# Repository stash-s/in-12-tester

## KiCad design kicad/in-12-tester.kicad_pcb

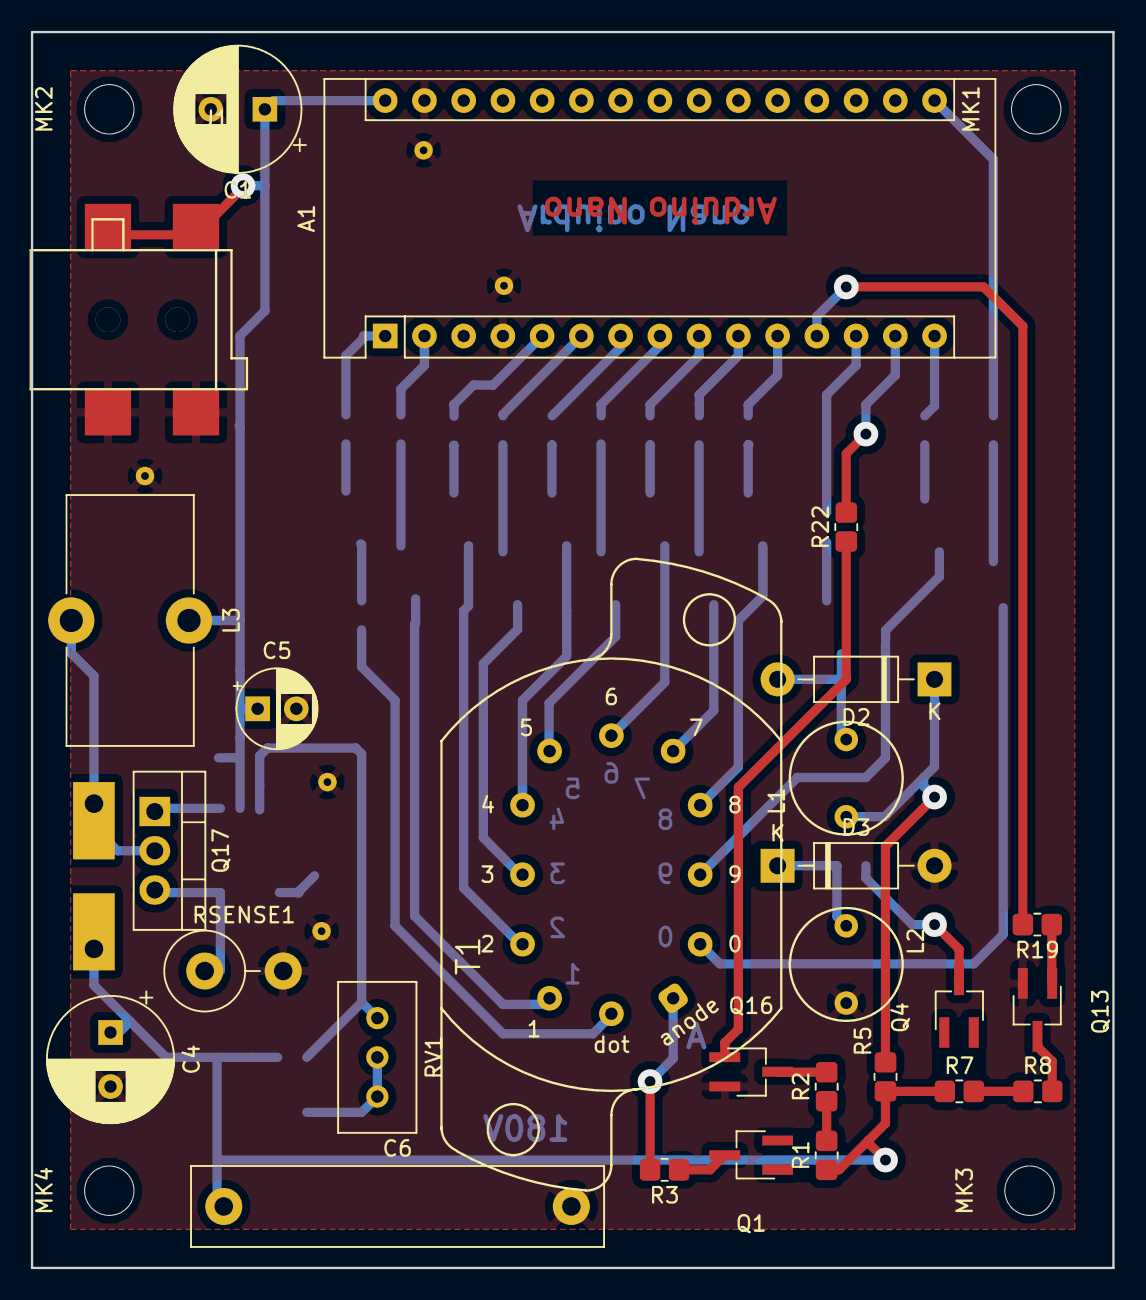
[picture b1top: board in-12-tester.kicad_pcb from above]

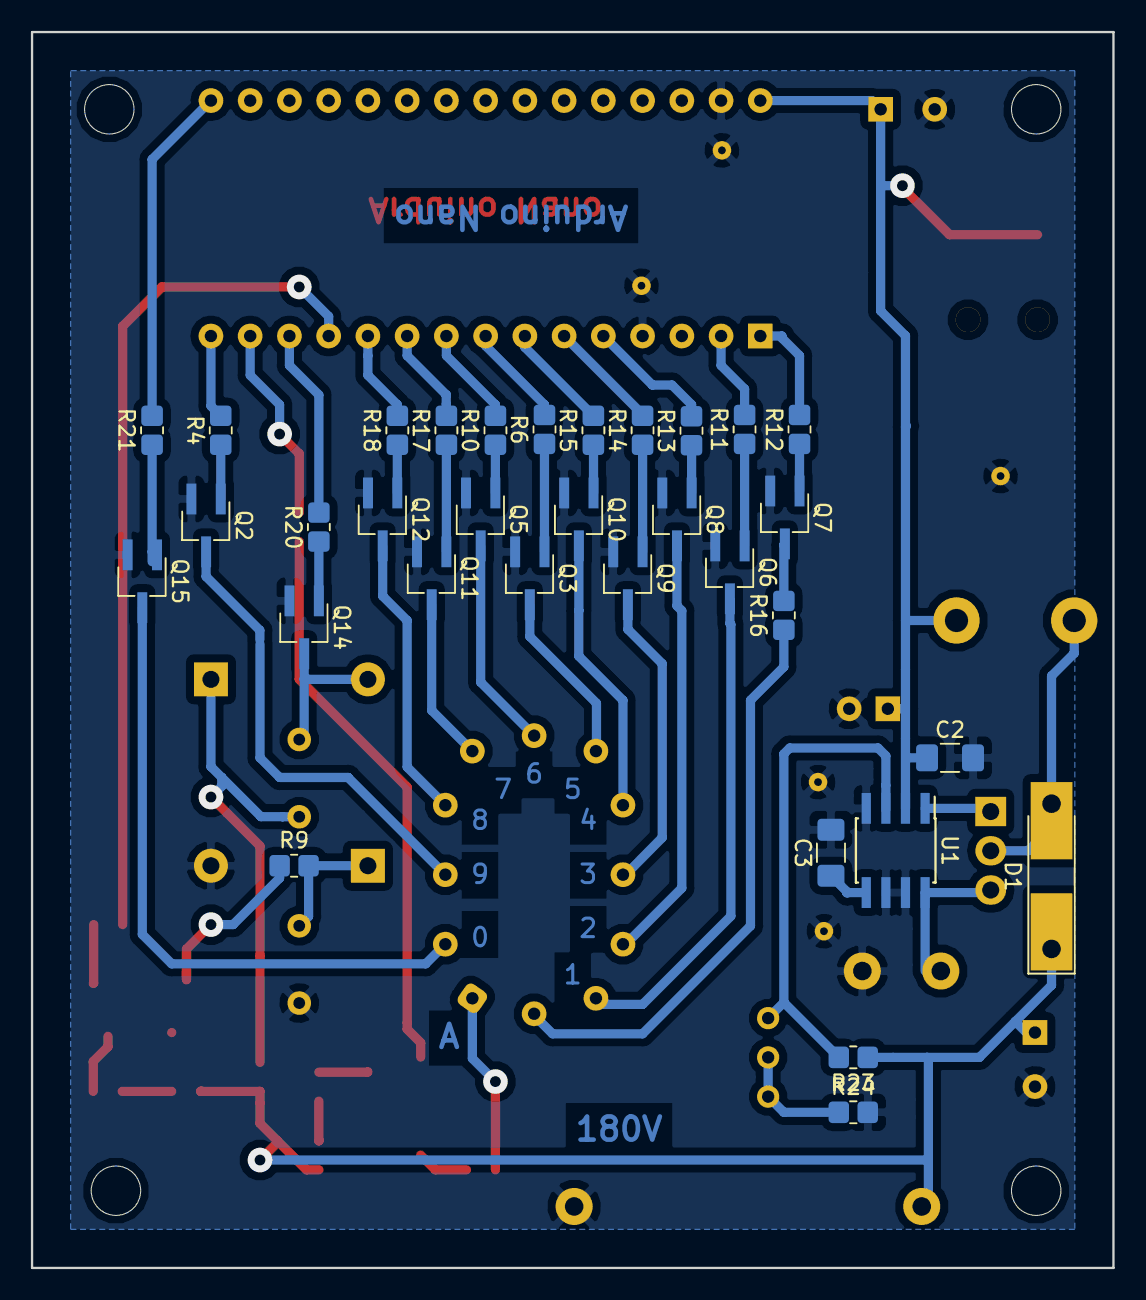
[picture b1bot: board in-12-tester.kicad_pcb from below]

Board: 2 copper layers, 70.0 x 80.0 mm, 68 parts (32 on the bottom side), 59 nets.

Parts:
A1: Arduino_Nano_v3.x; Arduino_Nano
C1: 100uF,25V; CP_Radial_D8.0mm_P3.50mm
C2, C3: 100n; C_1206_3216Metric_Pad1.42x1.75mm_HandSolder
C4: 4.7uF,250V; CP_Radial_D8.0mm_P3.50mm
C5: 10uF,25V; CP_Radial_D5.0mm_P2.50mm
C6: 100n,250V; C_Rect_L26.5mm_W5.0mm_P22.50mm_MKS4
D1: ES2J; D_MELF-RM10_Universal_Handsoldering
D2, D3: 100V; D_DO-41_SOD81_P10.16mm_Horizontal
J1: Jack-DC; AliExpress55mmBarelJack
L1, L2: ins-1
L3: L; L_Toroid_Vertical_L16.0mm_W8.0mm_P7.62mm
MK1, MK2, MK3, MK4: Mounting_Hole; MountingHole_3.2mm_M3
Q1, Q4: MMBTA92; TSOT-23_HandSoldering
Q2, Q5, Q6, Q7, Q8, Q9, Q10, Q11, Q12, Q13, Q14, Q15, Q16: MMBTA42; TSOT-23_HandSoldering
Q3: mmbta42; TSOT-23_HandSoldering
Q17: IRF740; TO-220-3_Vertical
R1, R2, R7, R8: 1M; R_0805_2012Metric_Pad1.33x1.40mm_HandSolder
R3: 10K; R_0805_2012Metric_Pad1.33x1.40mm_HandSolder
R4, R6, R11, R12, R13, R14, R15, R17, R18, R19, R20, R21, R22: 33K; R_0805_2012Metric_Pad1.33x1.40mm_HandSolder
R5, R9: 240K; R_0805_2012Metric_Pad1.33x1.40mm_HandSolder
R10: 33V; R_0805_2012Metric_Pad1.33x1.40mm_HandSolder
R16: 56K; R_0805_2012Metric_Pad1.33x1.40mm_HandSolder
R23: 1.5M; R_0805_2012Metric_Pad1.33x1.40mm_HandSolder
R24: 10k; R_0805_2012Metric_Pad1.33x1.40mm_HandSolder
RSENSE1: 0R1; R_Axial_DIN0516_L15.5mm_D5.0mm_P5.08mm_Vertical
RV1: 5K; Potentiometer_Bourns_3296W_Vertical
T1: IN-12; IN-12_0.8mm
U1: max1771; PowerIntegrations_SO-8
U3, U4, U5, U6, U7: THERMAL_VIA; Thermal Via

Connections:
+9V: A1.30, C1.1, C2.1, C5.1, J1.1, L3.1, U1.2
+VDC: C4.1, C6.1, D1.1, Q1.2, Q4.2, R1.1, R5.1, R7.1, R23.1
ANODE: A1.14, R22.2
D0: A1.16, R21.2
D1: A1.2, R11.2
D2: A1.5, R13.2
D3: A1.6, R14.2
D4: A1.7, R15.2
D5: A1.8, R6.2
D6: A1.9, R10.2
D7: A1.10, R17.2
D8: A1.11, R18.2
D9: A1.15, R4.2
DOT: A1.1, R12.2
DV: R16.1, T1.12
GND: A1.4, A1.29, C1.2, C2.2, C3.2, C4.2, C5.2, C6.2, D3.2, J1.2, L2.2, Q2.2, Q3.2, Q5.2, Q6.2, Q7.2, Q8.2, Q9.2, Q10.2, Q11.2, Q12.2, Q13.2, Q14.2, Q15.2, Q16.2, R24.2, RSENSE1.2, U1.4, U1.6, U1.7, U3.~, U4.~, U5.~, U6.~, U7.~
KHV0: Q15.3, T1.2
KHV1: Q6.3, T1.11
KHV2: Q8.3, T1.10
KHV3: Q9.3, T1.9
KHV4: Q10.3, T1.8
KHV5: Q3.3, T1.7
KHV6: Q5.3, T1.6
KHV7: Q11.3, T1.5
KHV8: Q12.3, T1.4
KHV9: Q2.3, T1.3
NEON1: A1.13, R20.2
NEON2: A1.12, R19.2
unnamed: C3.1, U1.5
unnamed: D1.2, L3.2, Q17.2
unnamed: D2.1, L1.1, R5.2
unnamed: D2.2, L1.2, Q14.3
unnamed: D3.1, L2.1, R9.2
unnamed: Q1.1, R1.2, R2.1
unnamed: Q1.3, R3.1
unnamed: Q2.1, R4.1
unnamed: Q3.1, R6.1
unnamed: Q4.1, R7.2, R8.1
unnamed: Q4.3, R9.1
unnamed: Q5.1, R10.1
unnamed: Q6.1, R11.1
unnamed: Q7.1, R12.1
unnamed: Q7.3, R16.2
unnamed: Q8.1, R13.1
unnamed: Q9.1, R14.1
unnamed: Q10.1, R15.1
unnamed: Q11.1, R17.1
unnamed: Q12.1, R18.1
unnamed: Q13.1, R19.1
unnamed: Q13.3, R8.2
unnamed: Q14.1, R20.1
unnamed: Q15.1, R21.1
unnamed: Q16.1, R22.1
unnamed: Q16.3, R2.2
unnamed: Q17.1, U1.1
unnamed: Q17.3, RSENSE1.1, U1.8
unnamed: R3.2, T1.1
unnamed: R23.2, RV1.3, U1.3
unnamed: R24.1, RV1.1, RV1.2

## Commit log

2018-07-26 Added kicad scheme and PCB.
2018-07-26 Added tester schematic.
2020-02-08 Updated and works with latest version of HW
